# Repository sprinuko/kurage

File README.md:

<p align="center">
	<br>
	kurage
</p>

qmk compatible, uses a promicro/other similar boards

designed to be fully hotswappable

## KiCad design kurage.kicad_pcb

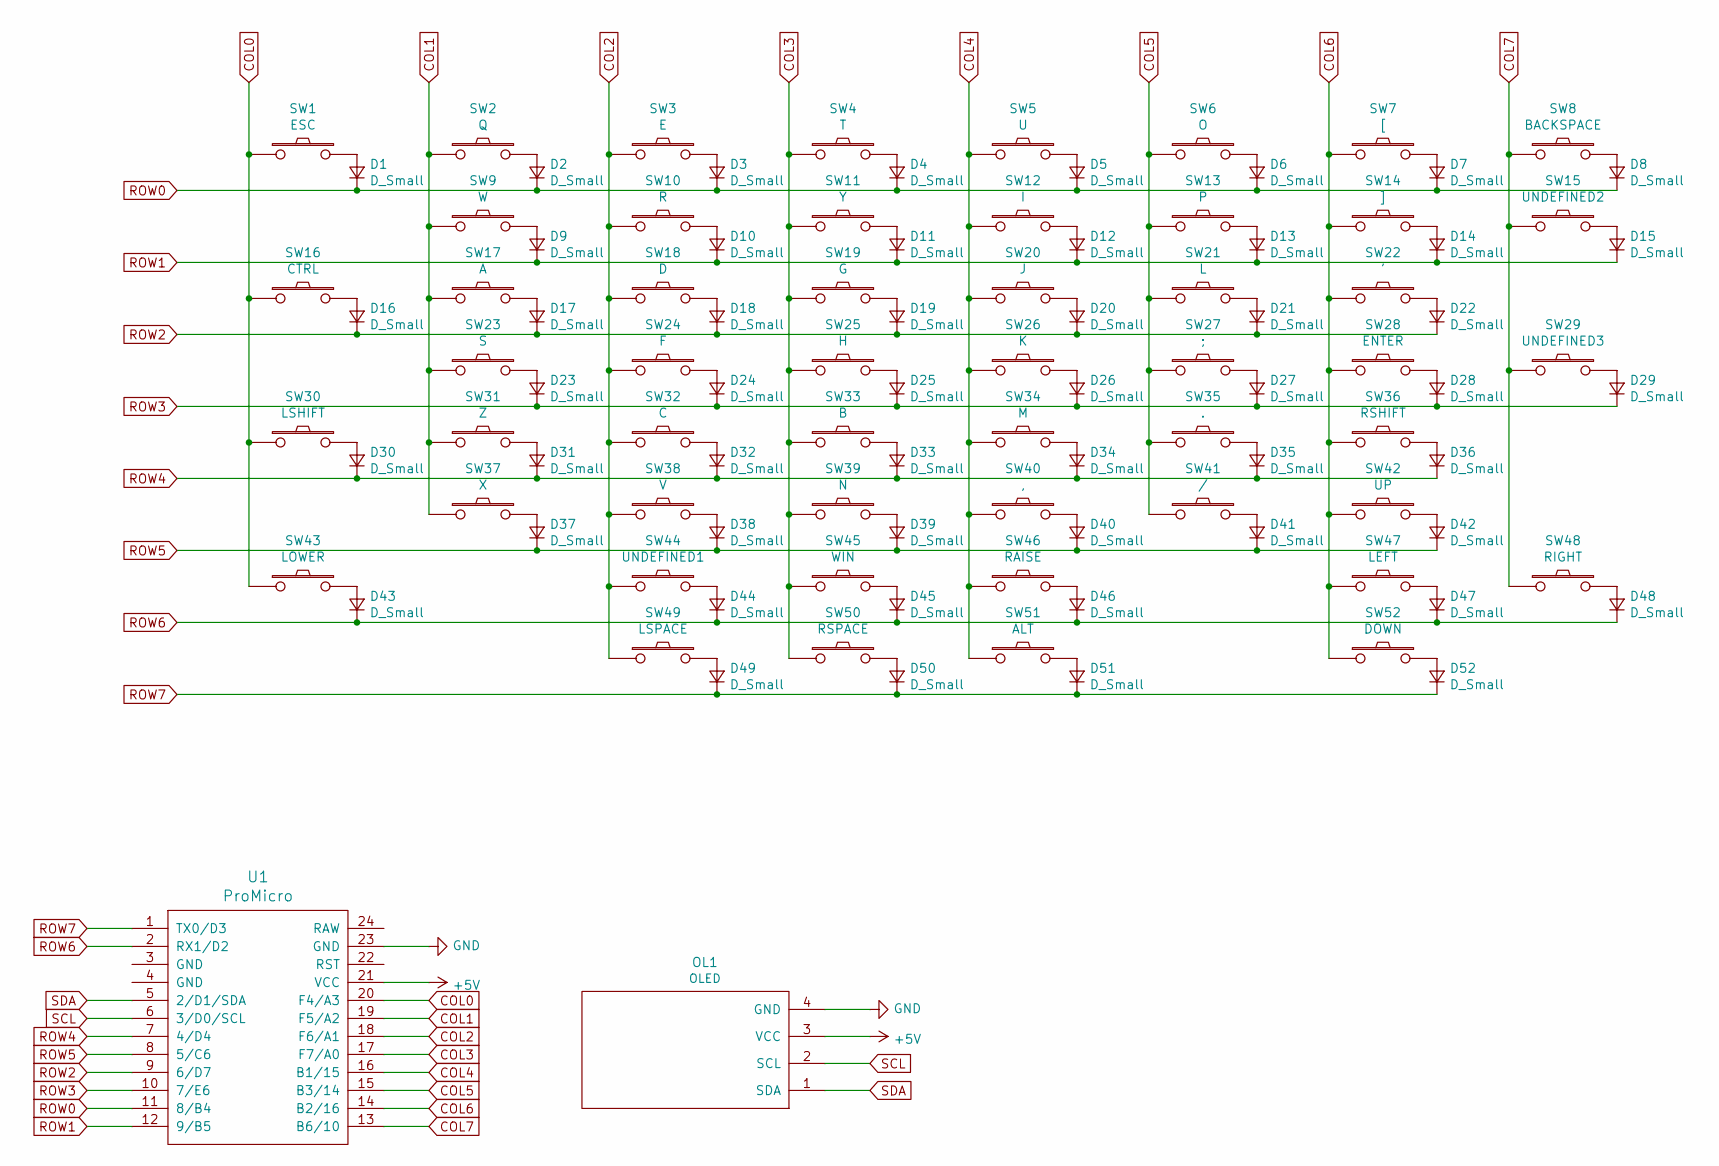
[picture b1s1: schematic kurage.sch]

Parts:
D1, D2, D3, D4, D5, D6, D7, D8, D9, D10, D11, D12, D13, D14, D15, D16, D17, D18, D19, D20, D21, D22, D23, D24, D25, D26, D27, D28, D29, D30, D31, D32, D33, D34, D35, D36, D37, D38, D39, D40, D41, D42, D43, D44, D45, D46, D47, D48, D49, D50, D51, D52: D_Small; D3_TH
OL1: OLED; OLED_v2
SW1: ESC; MXOnly-1.5U-Hotswap
SW2: Q; CherryMX_Hotswap
SW3: E; CherryMX_Hotswap
SW4: T; CherryMX_Hotswap
SW5: U; CherryMX_Hotswap
SW6: O; CherryMX_Hotswap
SW7: [; CherryMX_Hotswap
SW8: BACKSPACE; MXOnly-1.75U-Hotswap
SW9: W; CherryMX_Hotswap
SW10: R; CherryMX_Hotswap
SW11: Y; CherryMX_Hotswap
SW12: I; CherryMX_Hotswap
SW13: P; CherryMX_Hotswap
SW14: ]; CherryMX_Hotswap
SW15: UNDEFINED2; CherryMX_Hotswap
SW16: CTRL; MXOnly-1.75U-Hotswap
SW17: A; CherryMX_Hotswap
SW18: D; CherryMX_Hotswap
SW19: G; CherryMX_Hotswap
SW20: J; CherryMX_Hotswap
SW21: L; CherryMX_Hotswap
SW22: '; CherryMX_Hotswap
SW23: S; CherryMX_Hotswap
SW24: F; CherryMX_Hotswap
SW25: H; CherryMX_Hotswap
SW26: K; CherryMX_Hotswap
SW27: ;; CherryMX_Hotswap
SW28: ENTER; MXOnly-2.25U-Hotswap
SW29: UNDEFINED3; CherryMX_Hotswap
SW30: LSHIFT; MXOnly-2.25U-Hotswap
SW31: Z; CherryMX_Hotswap
SW32: C; CherryMX_Hotswap
SW33: B; CherryMX_Hotswap
SW34: M; CherryMX_Hotswap
SW35: .; CherryMX_Hotswap
SW36: RSHIFT; MXOnly-2U-Hotswap
SW37: X; CherryMX_Hotswap
SW38: V; CherryMX_Hotswap
SW39: N; CherryMX_Hotswap
SW40: ,; CherryMX_Hotswap
SW41: /; CherryMX_Hotswap
SW42: UP; CherryMX_Hotswap
SW43: LOWER; MXOnly-1.25U-Hotswap
SW44: UNDEFINED1; MXOnly-1.5U-Hotswap
SW45: WIN; CherryMX_Hotswap
SW46: RAISE; MXOnly-1.5U-Hotswap
SW47: LEFT; CherryMX_Hotswap
SW48: RIGHT; CherryMX_Hotswap
SW49: LSPACE; MXOnly-2U-Hotswap
SW50: RSPACE; MXOnly-2.75U-Hotswap
SW51: ALT; CherryMX_Hotswap
SW52: DOWN; CherryMX_Hotswap
U1: ProMicro; ProMicro_v3

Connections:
+5V: OL1.3 (VCC), U1.21 (VCC)
COL0: SW1.1, SW16.1, SW30.1, SW43.1, U1.20 (F4/A3)
COL1: SW2.1, SW9.1, SW17.1, SW23.1, SW31.1, SW37.1, U1.19 (F5/A2)
COL2: SW3.1, SW10.1, SW18.1, SW24.1, SW32.1, SW38.1, SW44.1, SW49.1, U1.18 (F6/A1)
COL3: SW4.1, SW11.1, SW19.1, SW25.1, SW33.1, SW39.1, SW45.1, SW50.1, U1.17 (F7/A0)
COL4: SW5.1, SW12.1, SW20.1, SW26.1, SW34.1, SW40.1, SW46.1, SW51.1, U1.16 (B1/15)
COL5: SW6.1, SW13.1, SW21.1, SW27.1, SW35.1, SW41.1, U1.15 (B3/14)
COL6: SW7.1, SW14.1, SW22.1, SW28.1, SW36.1, SW42.1, SW47.1, SW52.1, U1.14 (B2/16)
COL7: SW8.1, SW15.1, SW29.1, SW48.1, U1.13 (B6/10)
GND: OL1.4 (GND), U1.23 (GND)
unnamed: D1.2 (A), SW1.2
unnamed: D2.2 (A), SW2.2
unnamed: D3.2 (A), SW3.2
unnamed: D4.2 (A), SW4.2
unnamed: D5.2 (A), SW5.2
unnamed: D6.2 (A), SW6.2
unnamed: D7.2 (A), SW7.2
unnamed: D8.2 (A), SW8.2
unnamed: D9.2 (A), SW9.2
unnamed: D10.2 (A), SW10.2
unnamed: D11.2 (A), SW11.2
unnamed: D12.2 (A), SW12.2
unnamed: D13.2 (A), SW13.2
unnamed: D14.2 (A), SW14.2
unnamed: D15.2 (A), SW15.2
unnamed: D16.2 (A), SW16.2
unnamed: D17.2 (A), SW17.2
unnamed: D18.2 (A), SW18.2
unnamed: D19.2 (A), SW19.2
unnamed: D20.2 (A), SW20.2
unnamed: D21.2 (A), SW21.2
unnamed: D22.2 (A), SW22.2
unnamed: D23.2 (A), SW23.2
unnamed: D24.2 (A), SW24.2
unnamed: D25.2 (A), SW25.2
unnamed: D26.2 (A), SW26.2
unnamed: D27.2 (A), SW27.2
unnamed: D28.2 (A), SW28.2
unnamed: D29.2 (A), SW29.2
unnamed: D30.2 (A), SW30.2
unnamed: D31.2 (A), SW31.2
unnamed: D32.2 (A), SW32.2
unnamed: D33.2 (A), SW33.2
unnamed: D34.2 (A), SW34.2
unnamed: D35.2 (A), SW35.2
unnamed: D36.2 (A), SW36.2
unnamed: D37.2 (A), SW37.2
unnamed: D38.2 (A), SW38.2
unnamed: D39.2 (A), SW39.2
unnamed: D40.2 (A), SW40.2
unnamed: D41.2 (A), SW41.2
unnamed: D42.2 (A), SW42.2
unnamed: D43.2 (A), SW43.2
unnamed: D44.2 (A), SW44.2
unnamed: D45.2 (A), SW45.2
unnamed: D46.2 (A), SW46.2
unnamed: D47.2 (A), SW47.2
unnamed: D48.2 (A), SW48.2
unnamed: D49.2 (A), SW49.2
unnamed: D50.2 (A), SW50.2
unnamed: D51.2 (A), SW51.2
unnamed: D52.2 (A), SW52.2
ROW0: D1.1 (K), D2.1 (K), D3.1 (K), D4.1 (K), D5.1 (K), D6.1 (K), D7.1 (K), D8.1 (K), U1.11 (8/B4)
ROW1: D9.1 (K), D10.1 (K), D11.1 (K), D12.1 (K), D13.1 (K), D14.1 (K), D15.1 (K), U1.12 (9/B5)
ROW2: D16.1 (K), D17.1 (K), D18.1 (K), D19.1 (K), D20.1 (K), D21.1 (K), D22.1 (K), U1.9 (6/D7)
ROW3: D23.1 (K), D24.1 (K), D25.1 (K), D26.1 (K), D27.1 (K), D28.1 (K), D29.1 (K), U1.10 (7/E6)
ROW4: D30.1 (K), D31.1 (K), D32.1 (K), D33.1 (K), D34.1 (K), D35.1 (K), D36.1 (K), U1.7 (4/D4)
ROW5: D37.1 (K), D38.1 (K), D39.1 (K), D40.1 (K), D41.1 (K), D42.1 (K), U1.8 (5/C6)
ROW6: D43.1 (K), D44.1 (K), D45.1 (K), D46.1 (K), D47.1 (K), D48.1 (K), U1.2 (RX1/D2)
ROW7: D49.1 (K), D50.1 (K), D51.1 (K), D52.1 (K), U1.1 (TX0/D3)
SCL: OL1.2 (SCL), U1.6 (3/D0/SCL)
SDA: OL1.1 (SDA), U1.5 (2/D1/SDA)

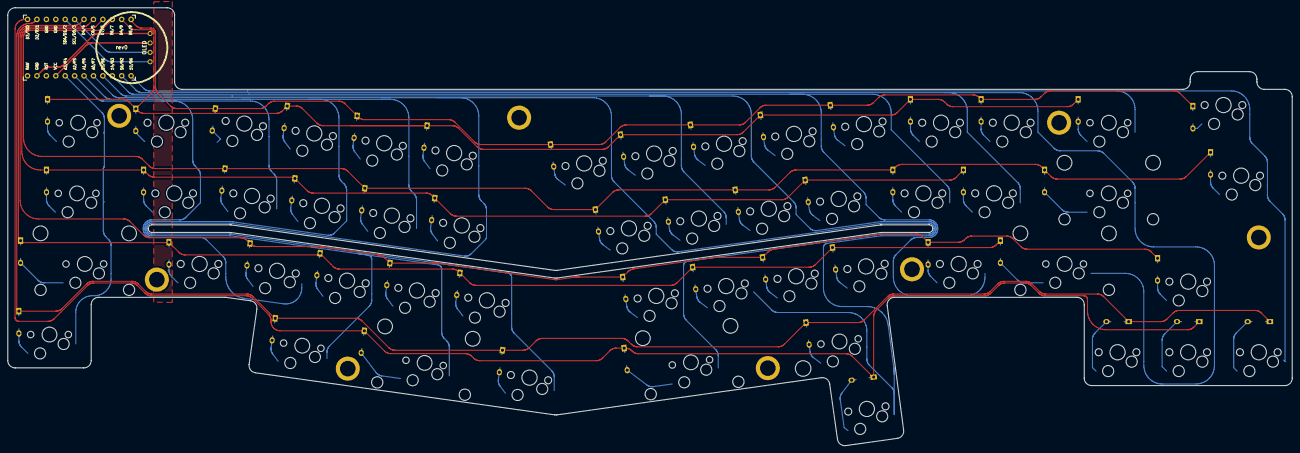
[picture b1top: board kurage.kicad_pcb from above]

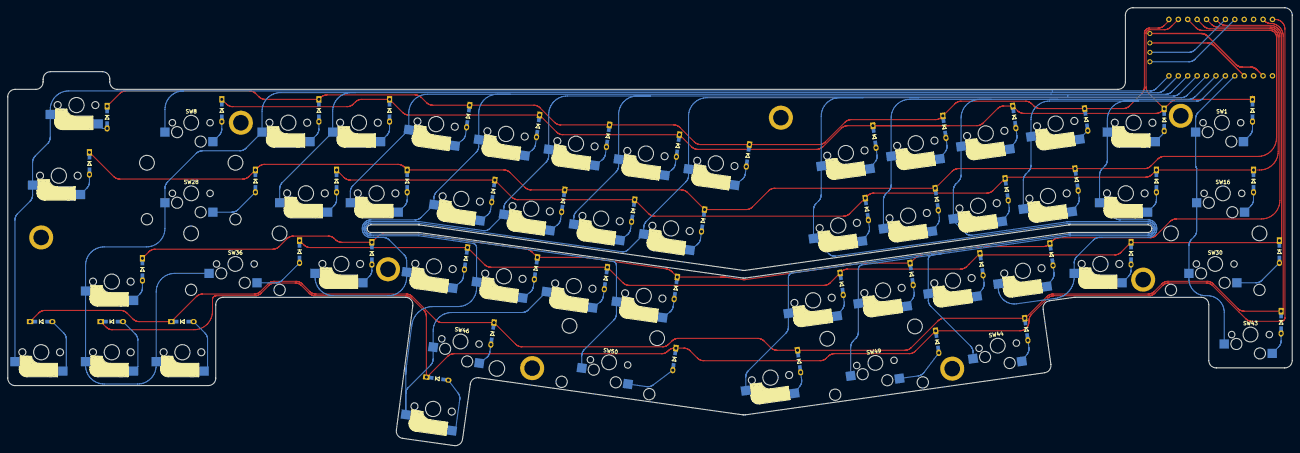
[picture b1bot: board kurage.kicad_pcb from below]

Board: 2 copper layers, 346.5 x 118.1 mm, 115 parts (52 on the bottom side), 72 nets.

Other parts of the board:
Ref**: Val**; M2_HOLE
Ref**#2, Ref**#3, Ref**#4, Ref**#5, Ref**#6, Ref**#7, Ref**#8: Val**; M2_HOLE
Ref**#9: Val**; M2_HOLE_v2

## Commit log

2020-09-30 init
2020-09-30 add submodules
2020-09-30 kicad init
2020-09-30 dxf files
2020-09-30 fix dxf
2020-09-30 schematic
2020-10-01 progress
2020-10-01 fixing
2020-10-01 remove submodule
2020-10-01 diodes
2020-10-01 progress 2
2020-10-01 save
2020-10-02 flip pro micro
2020-10-02 backup
2020-10-03 curved traces
2020-10-14 gerber
